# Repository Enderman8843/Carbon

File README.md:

# Carbon 

## Why did I build this 
As we know my nations air quality is pretty bad therefore I decided to make a air quality analyser to know the actual depth of this danger specially for my home 

## How to Use this 
First connect this device via usb-c cable to your pc then download the firmware files `Firmware\BUILD` or build them using the ino file in `firmware` wait for sometime as the BME688 needs sometime to stabilize its reading then after that the neopixels will show the color according to the IAQ of your enviroiment (RED = BAD , GREEN = GOOD , AMBER= MODERATE)

*Note the firmware is untested

## Working 
This takes the reading of the Bosch IAQ sensor and the temperature sensor to give accurate condition of the enviroiment 

## PCB Layout

| PCB Layout | Schematic / Wiring |
| :---------: | :----------------: |
|  |  |

## PCB Render

| Front | Rear |
| :---: | :--: |
|  |  |

## Case

---

## BOM

| Item | Description | Quantity | Unit Price ($) | Total Price ($) | URL |
|------|-------------|----------|----------------|-----------------|-----|
| PCBA | Custom PCB Manufacturing (JLCPCB) | 1 | 49.35 | 49.35 | https://jlcpcb.com |
| Case | 3D Printed Case (Will be Printed Myself | 1 | 0.00 | 0.00 | https://hackclub.com |
| ESP-32 C6 Mini-1 | MCU |1 | 4.47 | 4.47 |  https://www.digikey.in/en/products/detail/espressif-systems/ESP32-C6-MINI-1-N4/17885796 |
| BME688 | VOC sensor | 1 | 9 |  9  | https://www.digikey.in/en/products/detail/bosch-sensortec/BME688/13681261|
| **TOTAL** |  |  |  | **63.00** |  |

# JLCPCB and Shipping

---

## BOM PCBA 
# BOM (Bill of Materials)

| Comment | Designator | Footprint | LCSC | Quantity |
|---|---|---|---|---:|
| 0.1uF | C13, C15, C3, C4, C5, C7, C8 | C_0603_1608Metric | C125205 | 7 |
| 10K | R1, R2 | R_0603_1608Metric | C15401 | 2 |
| 10uF | C10, C12, C14, C9 | C_0603_1608Metric | C19702 | 4 |
| 1uF | C11 | C_0603_1608Metric | C15849 | 1 |
| 220Ω | R5 | R_0603_1608Metric | C23179 | 1 |
| 4.7kΩ | R10, R9 | R_0603_1608Metric | C15401 | 2 |
| 47uF | C6 | C_0603_1608Metric | C140782 | 1 |
| 5.1kΩ | R6, R7 | R_0603_1608Metric | C23186 | 2 |
| 74AHCT1G125SE-7 | U7 | SOT-353_L2.2-W1.4-P0.65-LS2.4-BR | C151417 | 1 |
| AP2112K-3.3TRG1 | U5 | SOT-25-5_L2.9-W1.6-P0.95-LS2.8-BL | C51118 | 1 |
| AP2120N-1.8TRG1 | U4 | SOT-23_L2.9-W1.3-P1.90-LS2.4-BR | C460317 | 1 |
| BME688 | U6 | LGA-8_L3.0-W3.0-P0.80_BME688 | C3664478 | 1 |
| ENS210 | U1 | AMS_QFN-4-1EP_2x2mm_P0.95mm_EP0.7x1.6mm | C2991202 | 1 |
| ESP32-C6-MINI-1 | U3 | ESP32-C6-MINI-1 | C5736265 | 1 |
| SW_Push | Boot1, Reset1 | SW_SPST_PTS647_Sx38 | C720477 | 2 |
| USB-C Receptacle USB2.0 14P | J1 | USB_C_Receptacle_HRO_TYPE-C-31-M-12 | C5143397 | 1 |
| SK6812MINI | D1 | LED_SK6812MINI_PLCC4_3.5x3.5mm_P1.75mm | — | 1 |
| SK6812MINI | D2 | LED_SK6812MINI_PLCC4_3.5x3.5mm_P1.75mm | — | 1 |

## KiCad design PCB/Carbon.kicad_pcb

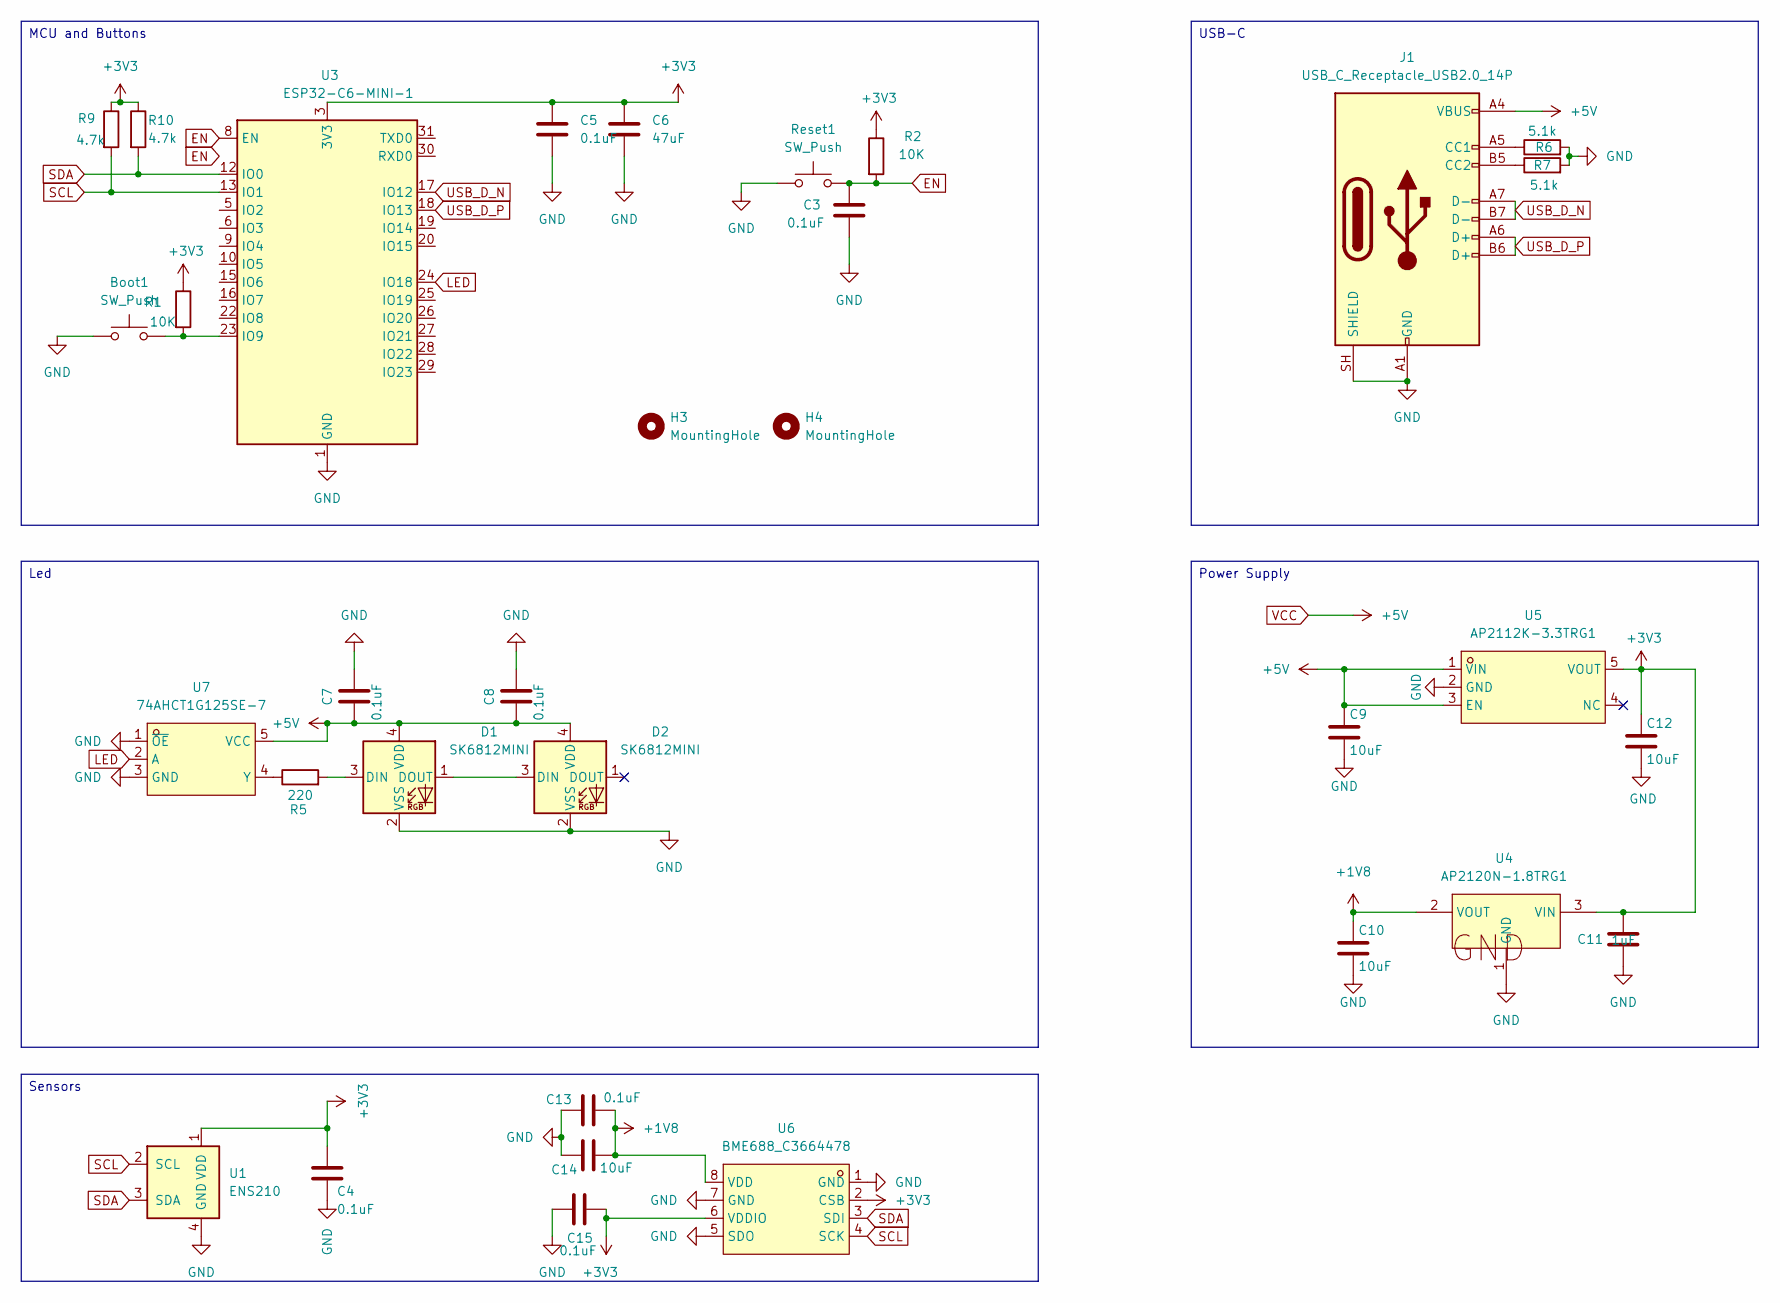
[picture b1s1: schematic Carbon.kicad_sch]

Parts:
Boot1: SW_Push; SW_SPST_PTS647_Sx38
C3, C4, C5, C7, C8, C13, C15: 0.1uF; C_0603_1608Metric
C6: 47uF; C_0603_1608Metric
C9, C10, C12, C14: 10uF; C_0603_1608Metric
C11: 1uF; C_0603_1608Metric
D1, D2: SK6812MINI; LED_SK6812MINI_PLCC4_3.5x3.5mm_P1.75mm
H3, H4: MountingHole; MountingHole_2.2mm_M2
J1: USB_C_Receptacle_USB2.0_14P; USB_C_Receptacle_HRO_TYPE-C-31-M-12
R1, R2: 10K; R_0603_1608Metric
R5: 220; R_0603_1608Metric
R6, R7: 5.1k; R_0603_1608Metric
R9, R10: 4.7k; R_0603_1608Metric
Reset1: SW_Push; SW_SPST_PTS647_Sx38
U1: ENS210; AMS_QFN-4-1EP_2x2mm_P0.95mm_EP0.7x1.6mm
U3: ESP32-C6-MINI-1
U4: AP2120N-1.8TRG1; SOT-23_L2.9-W1.3-P1.90-LS2.4-BR; MPN AP2120N-1.8TRG1; LCSC Part C460317
U5: AP2112K-3.3TRG1; SOT-25-5_L2.9-W1.6-P0.95-LS2.8-BL; MPN AP2112K-3.3TRG1; LCSC Part C51118
U6: BME688_C3664478; LGA-8_L3.0-W3.0-P0.80_BME688; MPN BME688; LCSC Part C3664478
U7: 74AHCT1G125SE-7; SOT-353_L2.2-W1.4-P0.65-LS2.4-BR; MPN 74AHCT1G125SE-7; LCSC Part C151417

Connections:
+1V8: C10.1, C13.1, C14.1, U4.2 (VOUT), U6.8 (VDD)
+3V3: C4.1, C5.1, C6.1, C11.1, C12.1, C15.2, R1.1, R2.1, R9.1, R10.1, U1.1 (VDD), U3.3 (3V3), U4.3 (VIN), U5.5 (VOUT), U6.2 (CSB), U6.6 (VDDIO)
EN: C3.1, R2.2, Reset1.2, U3.8 (EN)
GND: Boot1.1, C3.2, C4.2, C5.2, C6.2, C7.2, C8.2, C9.2, C10.2, C11.2, C12.2, C13.2, C14.2, C15.1, D1.2 (VSS), D2.2 (VSS), J1.A1 (GND), J1.A12 (GND), J1.B1 (GND), J1.B12 (GND), J1.SH (SHIELD), R6.2, R7.2, Reset1.1, U1.4 (GND), U1.5 (GND), U3.1 (GND), U3.2 (GND), U3.11 (GND), U3.14 (GND), U3.36 (GND), U3.37 (GND), U3.38 (GND), U3.39 (GND), U3.40 (GND), U3.41 (GND), U3.42 (GND), U3.43 (GND), U3.44 (GND), U3.45 (GND), U3.46 (GND), U3.47 (GND), U3.48 (GND), U3.49 (GND), U3.50 (GND), U3.51 (GND), U3.52 (GND), U3.53 (GND), U4.1 (GND), U5.2 (GND), U6.1 (GND), U6.5 (SDO), U6.7 (GND), U7.1 (~OE), U7.3 (GND)
LED: U3.24 (IO18), U7.2 (A)
unnamed: D1.3 (DIN), R5.2
unnamed: D1.1 (DOUT), D2.3 (DIN)
unnamed: J1.A5 (CC1), R6.1
unnamed: J1.B5 (CC2), R7.1
unnamed: Boot1.2, R1.2, U3.23 (IO9)
unnamed: R5.1, U7.4 (Y)
SCL: R9.2, U1.2 (SCL), U3.13 (IO1), U6.4 (SCK)
SDA: R10.2, U1.3 (SDA), U3.12 (IO0), U6.3 (SDI)
USB_D_N: J1.A7 (D-), J1.B7 (D-), U3.17 (IO12)
USB_D_P: J1.A6 (D+), J1.B6 (D+), U3.18 (IO13)
VCC: C7.1, C8.1, C9.1, D1.4 (VDD), D2.4 (VDD), J1.A4 (VBUS), J1.A9 (VBUS), J1.B4 (VBUS), J1.B9 (VBUS), U5.1 (VIN), U5.3 (EN), U7.5 (VCC)

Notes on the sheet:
Led
Sensors
Power Supply
USB-C
MCU and Buttons

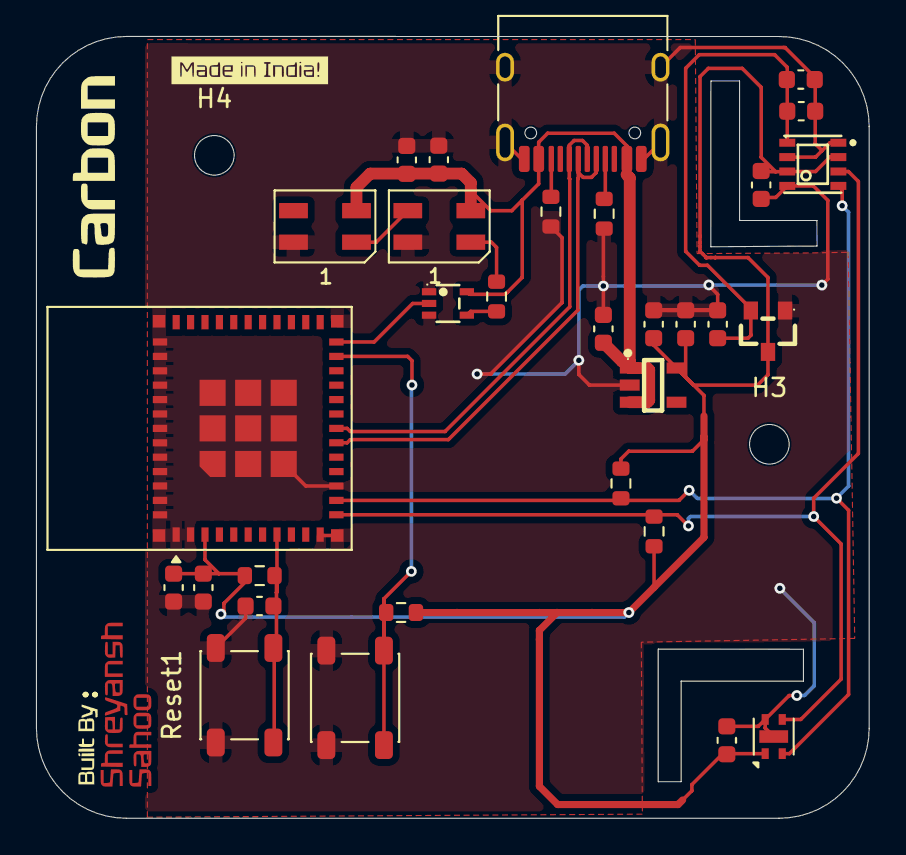
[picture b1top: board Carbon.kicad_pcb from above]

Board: 2 copper layers, 46.3 x 43.4 mm, 33 parts (0 on the bottom side), 16 nets.

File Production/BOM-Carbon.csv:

Comment,Designator,Footprint,LCSC,Quantity
0.1uF,"C13,C15,C3,C4,C5,C7,C8",C_0603_1608Metric,C125205,7
10K,"R1,R2",R_0603_1608Metric,C15401,2
10uF,"C10,C12,C14,C9",C_0603_1608Metric,C19702,4
1uF,C11,C_0603_1608Metric,C15849,1
220,R5,R_0603_1608Metric,C23179,1
4.7k,"R10,R9",R_0603_1608Metric,C15401,2
47uF,C6,C_0603_1608Metric,C140782,1
5.1k,"R6,R7",R_0603_1608Metric,C23186,2
74AHCT1G125SE-7,U7,SOT-353_L2.2-W1.4-P0.65-LS2.4-BR,C151417,1
AP2112K-3.3TRG1,U5,SOT-25-5_L2.9-W1.6-P0.95-LS2.8-BL,C51118,1
AP2120N-1.8TRG1,U4,SOT-23_L2.9-W1.3-P1.90-LS2.4-BR,C460317,1
BME688_C3664478,U6,LGA-8_L3.0-W3.0-P0.80_BME688,C3664478,1
ENS210,U1,AMS_QFN-4-1EP_2x2mm_P0.95mm_EP0.7x1.6mm,C2991202,1
ESP32-C6-MINI-1,U3,ESP32-C6-MINI-1,C5736265,1
SW_Push,"Boot1,Reset1",SW_SPST_PTS647_Sx38,C720477,2
USB_C_Receptacle_USB2.0_14P,J1,USB_C_Receptacle_HRO_TYPE-C-31-M-12,C5143397,1
SK6812MINI,D1,LED_SK6812MINI_PLCC4_3.5x3.5mm_P1.75mm,,1
SK6812MINI,D2,LED_SK6812MINI_PLCC4_3.5x3.5mm_P1.75mm,,1
